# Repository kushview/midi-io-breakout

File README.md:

# MIDI IO Breakout

A breakout board for Arduino that provides MIDI input and output over UART. The design was done in KiCad.

### Resources
* [Bill of Materials](doc/BOM.md)
* [Design Files](midi_io)
* [Example Sketches](examples)

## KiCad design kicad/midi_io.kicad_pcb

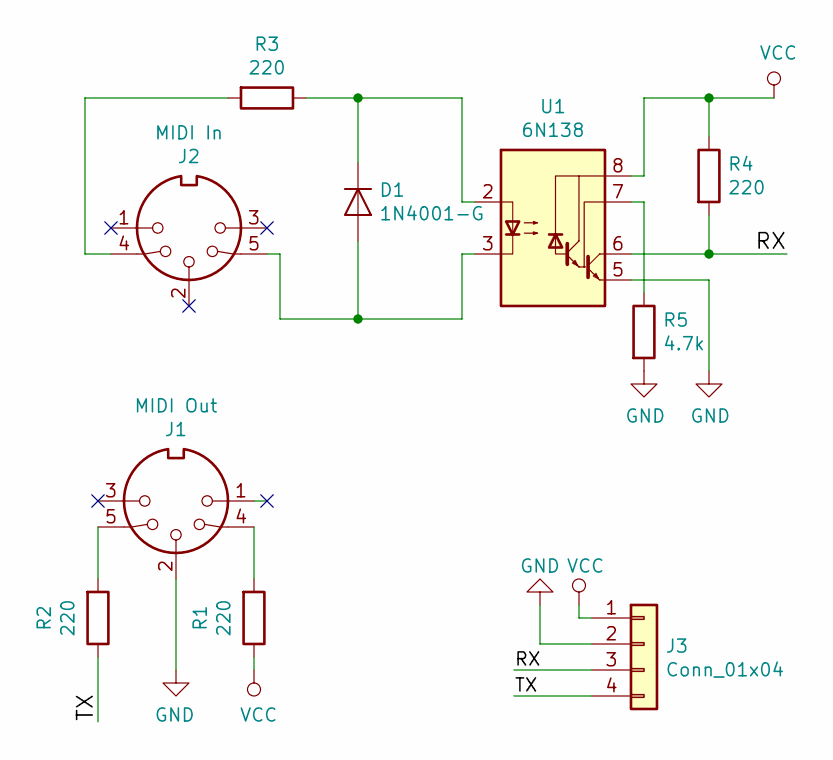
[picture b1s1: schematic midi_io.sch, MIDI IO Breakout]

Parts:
D1: 1N4001-G; D_DO-41_SOD81_P7.62mm_Horizontal
J1: MIDI Out; CUI_SDS-50J
J2: MIDI In; CUI_SDS-50J
J3: Conn_01x04; PinHeader_1x04_P2.54mm_Vertical
R1, R2, R3, R4: 220; R_0805_2012Metric_Pad1.15x1.40mm_HandSolder
R5: 4.7k; R_0805_2012Metric_Pad1.15x1.40mm_HandSolder
U1: 6N138; DIP-8_W7.62mm

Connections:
/RX: J3.3, R4.2, U1.6 (VO2)
/TX: J3.4, R2.1
GND: J1.2, J3.2, R5.2, U1.5 (GND)
unnamed: D1.1 (K), R3.1, U1.2 (C1)
unnamed: D1.2 (A), J2.5, U1.3 (C2)
unnamed: J1.4, R1.2
unnamed: J1.5, R2.2
unnamed: J2.4, R3.2
unnamed: R5.1, U1.7 (VO1)
VCC: J3.1, R1.1, R4.1, U1.8 (VCC)

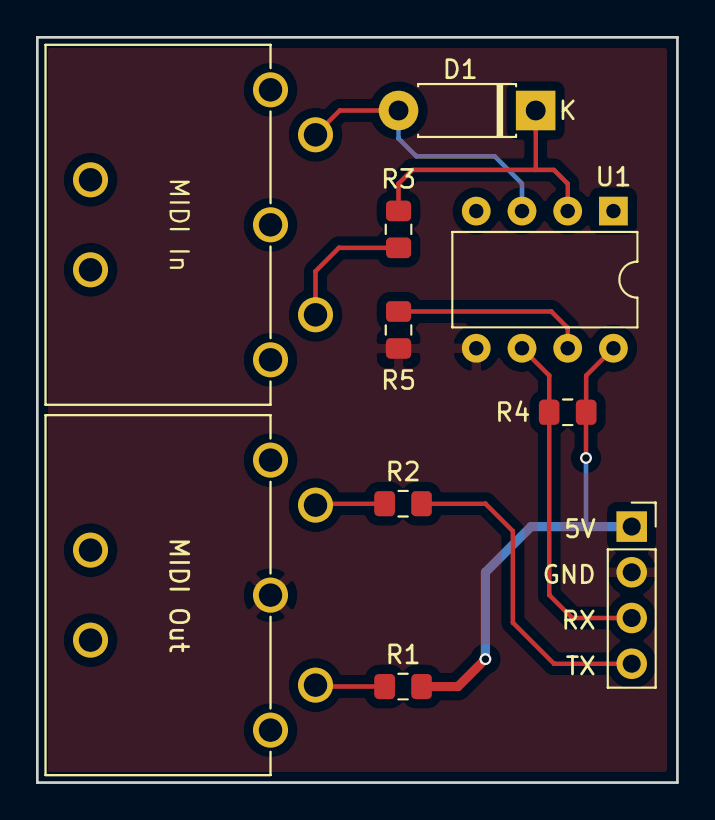
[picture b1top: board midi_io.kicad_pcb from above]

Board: 2 copper layers, 35.6 x 41.4 mm, 10 parts (0 on the bottom side), 10 nets.

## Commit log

2020-01-16 Initial revision
2020-01-16 Added basic midi input arduino example
2020-02-03 Update design
2020-02-03 Update gitignore
2020-02-04 Change to 0804 SMD resistors
2020-02-04 Re-route PCB
2020-02-04 UPdate meta, tweak traces
2020-02-05 Possible final PCB layout
2020-02-06 Misc
2020-02-10 Update with fixes from first prototype
2020-02-17 Update cache
2020-02-22 Use larger spacing/via sizes
2020-03-02 Rename MIDI input example
2020-03-02 Updating min via sizes
2020-03-03 Generate gerbers
2020-03-03 Updated info cache
2020-03-03 Moved kicad dir to midi_io
2020-03-03 Rename 5V silk to VCC
2020-03-03 Regen gerbers
2020-03-03 Added MIDI Output example
2020-03-03 Tidy up input/output examples
2020-03-04 Added script that zips gerber files
2020-03-04 Clean up fab layer labels
2020-03-04 bak file updated
2020-03-04 Update gerbers
2020-03-04 Update gerbers.sh + gbr files
2020-03-04 Exclude gerbers from git
2020-04-09 Info cache updated
2020-04-09 Housekeeping
2020-04-09 Update readme and BOM
2020-05-18 Update project file
